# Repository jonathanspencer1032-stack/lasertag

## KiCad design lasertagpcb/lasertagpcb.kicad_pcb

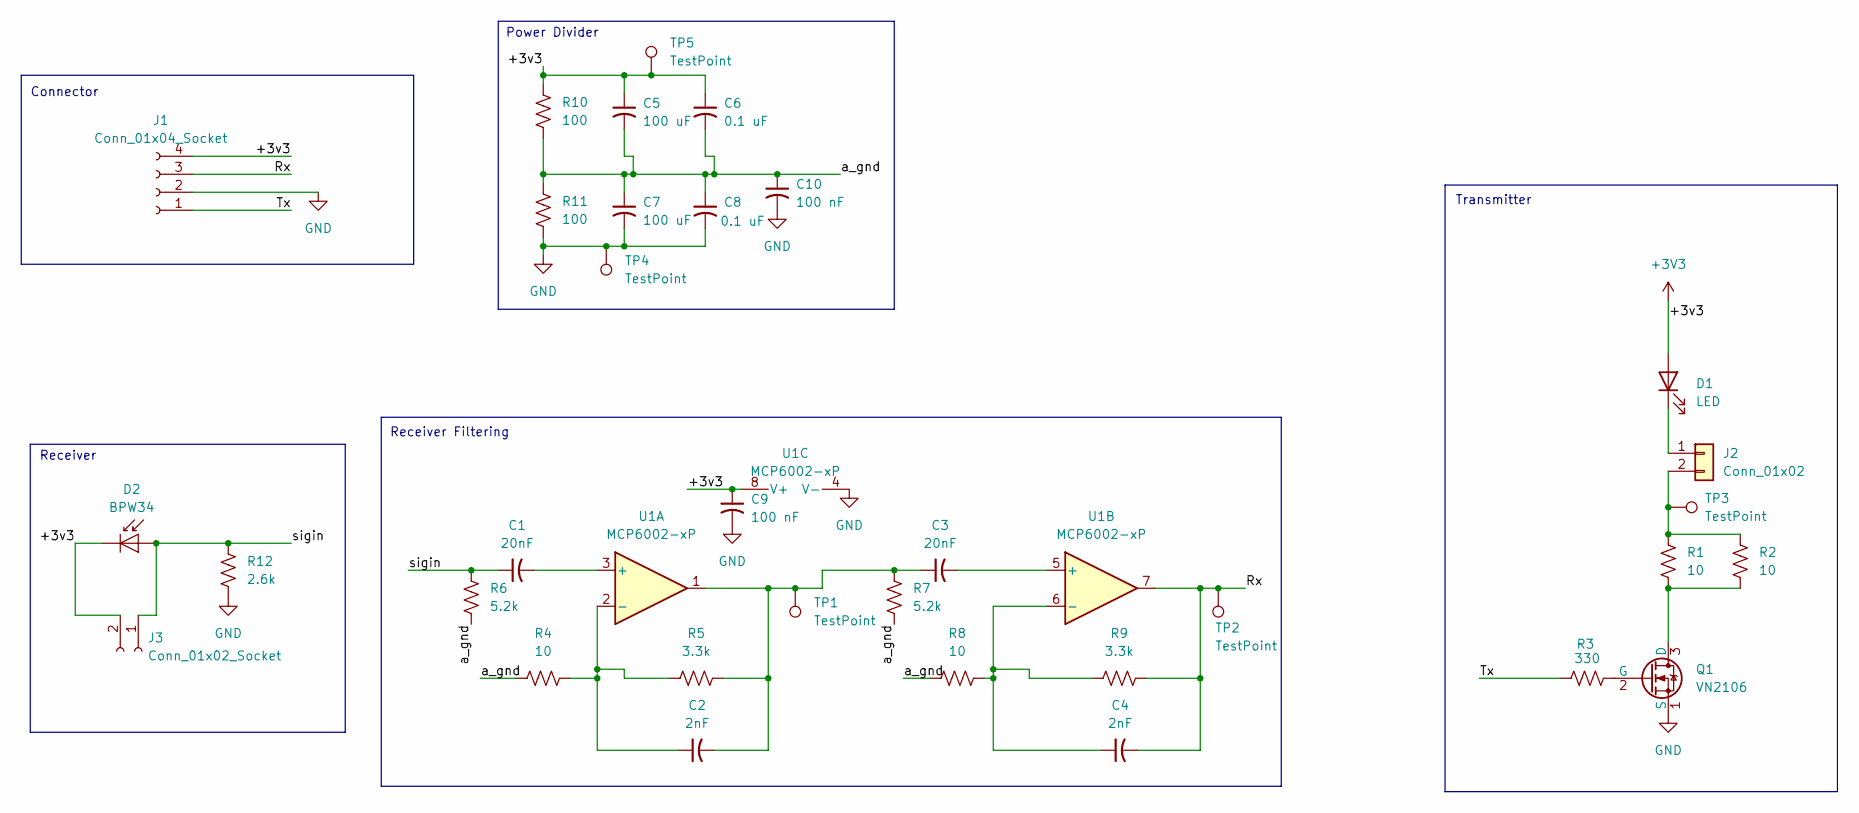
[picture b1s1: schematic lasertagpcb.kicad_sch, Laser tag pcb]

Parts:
C1, C3: 20nF; C_0805_2012Metric_Pad1.18x1.45mm_HandSolder
C2, C4: 2nF; C_0805_2012Metric_Pad1.18x1.45mm_HandSolder
C5, C7: 100 uF; CP_Radial_D10.0mm_P5.00mm
C6, C8: 0.1 uF; C_0805_2012Metric_Pad1.18x1.45mm_HandSolder
C9, C10: 100 nF; C_0805_2012Metric_Pad1.18x1.45mm_HandSolder
D1: LED; LED_D3.0mm
D2: BPW34; Osram_DIL2_4.3x4.65mm_P5.08mm
J1: Conn_01x04_Socket; PinSocket_1x04_P2.54mm_Vertical
J2: Conn_01x02; PinHeader_1x02_P2.54mm_Vertical
J3: Conn_01x02_Socket; JST_PH_B2B-PH-K_1x02_P2.00mm_Vertical
Q1: VN2106; TO-92_Inline
R1, R2, R4, R8: 10; R_0805_2012Metric_Pad1.20x1.40mm_HandSolder
R3: 330; R_0805_2012Metric_Pad1.20x1.40mm_HandSolder
R5, R9: 3.3k; R_0805_2012Metric_Pad1.20x1.40mm_HandSolder
R6, R7: 5.2k; R_0805_2012Metric_Pad1.20x1.40mm_HandSolder
R10, R11: 100; R_0805_2012Metric_Pad1.20x1.40mm_HandSolder
R12: 2.6k; R_0805_2012Metric_Pad1.20x1.40mm_HandSolder
TP1, TP2, TP3, TP4, TP5: TestPoint; TestPoint_Pad_2.0x2.0mm
U1: MCP6002-xP; DIP-8_W7.62mm

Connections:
+3V3: C5.1, C6.1, C9.1, D1.2 (A), D2.1 (K), J1.4, J3.2, R10.2, TP5.1, U1.8 (V+)
/Rx: C4.2, J1.3, R9.2, TP2.1, U1.7
/Tx: J1.1, R3.1
/a_gnd: C5.2, C6.2, C7.1, C8.1, C10.1, R4.1, R6.1, R7.1, R8.1, R10.1, R11.2
/sigin: C1.1, D2.2 (A), J3.1, R6.2, R12.2
GND: C7.2, C8.2, C9.2, C10.2, J1.2, Q1.1 (S), R11.1, R12.1, TP4.1, U1.4 (V-)
unnamed: C2.2, C3.1, R5.2, R7.2, TP1.1, U1.1
unnamed: D1.1 (K), J2.1
unnamed: J2.2, R1.1, R2.1, TP3.1
unnamed: Q1.3 (D), R1.2, R2.2
unnamed: Q1.2 (G), R3.2
unnamed: C1.2, U1.3 (+)
unnamed: C2.1, R4.2, R5.1, U1.2 (-)
unnamed: C3.2, U1.5 (+)
unnamed: C4.1, R8.2, R9.1, U1.6 (-)

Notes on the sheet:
Receiver
Transmitter
Connector
Power Divider
Receiver Filtering

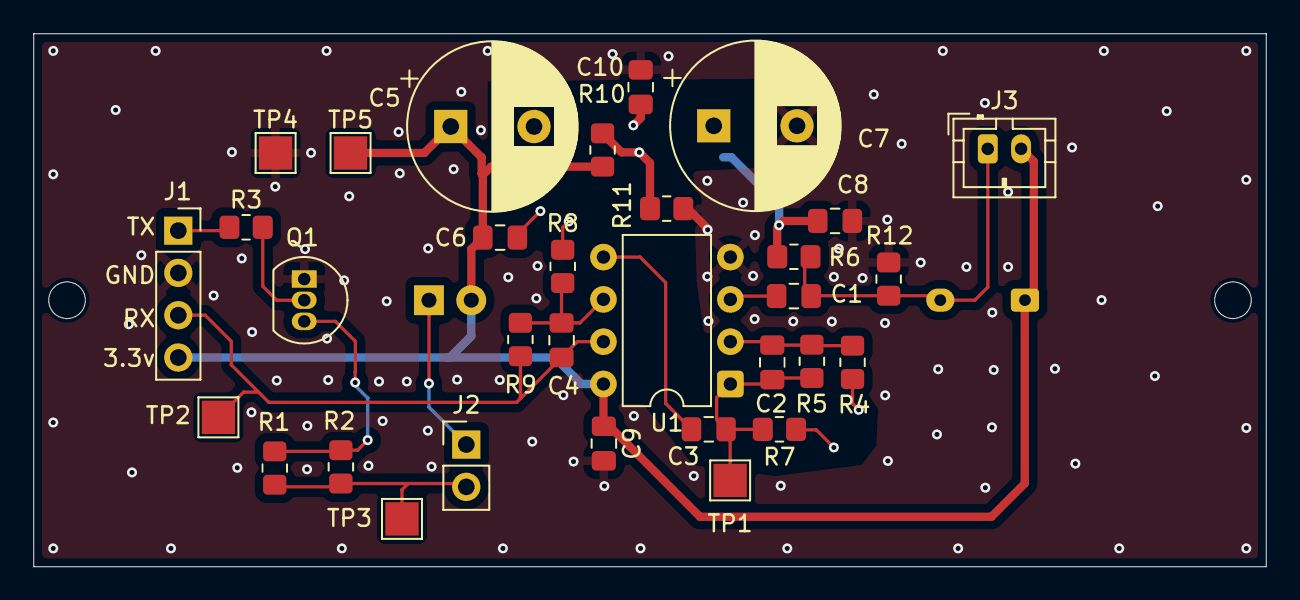
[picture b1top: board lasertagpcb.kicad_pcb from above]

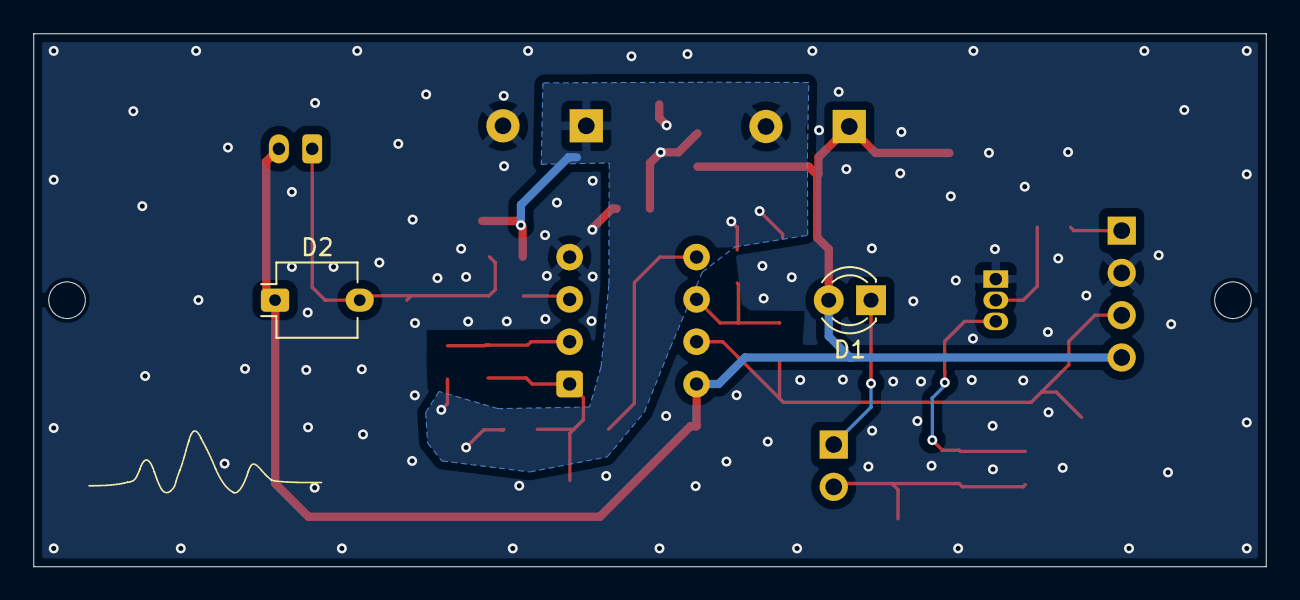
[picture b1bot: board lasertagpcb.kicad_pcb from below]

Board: 2 copper layers, 74.0 x 32.0 mm, 34 parts (2 on the bottom side), 15 nets.

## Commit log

2025-10-23 added .gitignore
2025-10-23 soldermask updates
2025-10-23 Create README.md
    Added README
2025-10-23 updated photo diode
2025-10-23 Save local KiCad changes before pull
2025-10-24 Updated layout. Added decoupling caps
